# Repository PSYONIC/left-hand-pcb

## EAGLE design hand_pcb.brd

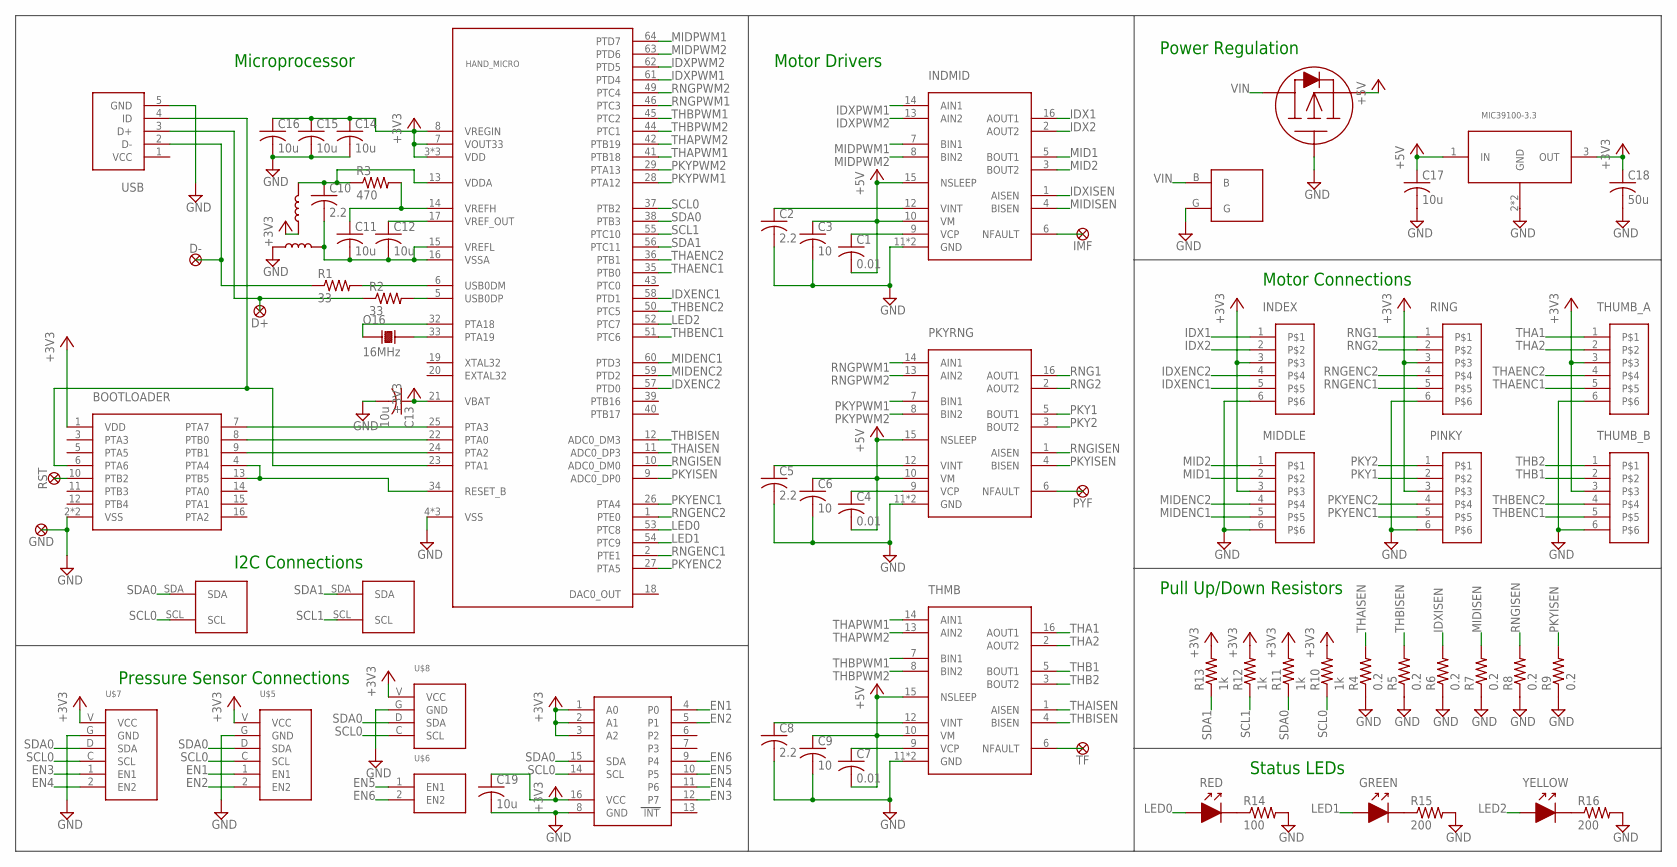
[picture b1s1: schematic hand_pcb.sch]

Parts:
BOOTLOADER: MKL02Z32CORRECT; QFN16
C1, C4, C7: 0.01; C0603
C2, C5, C8: 2.2; C0603
C3, C6, C9: 10; C0603
C10: 2.2; C0402
C11, C12, C13, C14, C15, C16, C19: 10u; C0402
C17: 10u; C0603
C18: 50u; C0603
D+: TESTPAD
D-: TESTPAD
GND: TESTPAD
GREEN: LED0603; L0603
HAND_MICRO: MK20DX256VLH7; LQFP-64-10-10
IMF: TESTPAD
INDEX: DF57H-6PTOP; DF57H-6P-TOP
INDMID: DRV8833; WQFN-16
MIDDLE: DF57H-6PTOP; DF57H-6P-TOP
O16: 16MHz; NX3225SA
PINKY: DF57H-6PTOP; DF57H-6P-TOP
PKYRNG: DRV8833; WQFN-16
PYF: TESTPAD
R1, R2: 33; R0402
R3: 470; R0402
R4, R5, R6, R7, R8, R9: 0.2; R1206
R10, R11, R12, R13: 1k; R0603
R14: 100; R0603
R15, R16: 200; R0603
RED: LED0603; L0603
RING: DF57H-6PTOP; DF57H-6P-TOP
RST: TESTPAD
TF: TESTPAD
THMB: DRV8833; WQFN-16
THUMB_A: DF57H-6PTOP; DF57H-6P-TOP
THUMB_B: DF57H-6PTOP; DF57H-6P-TOP
U$1: TCA9534TSSOP; TSSOP16
U$2: SPD15P10PLG; PG-TO-252-3
U$3, U$4: FERRITE600OHM100MHZ; L0603
U$5, U$7: PSENSE
U$6: PSENSE2
U$8: PSENSE4
U$9: MIC391003.3; MIC39100
U$10: THRUHOLE2
U$11, U$12: THRUHOLEI2C
USB: 10118194-0001LF
YELLOW: LED0603; L0603

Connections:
+3V3: BOOTLOADER.1 (VDD), C13.1, C14.1, C15.1, C16.1, C18.1, C19.1, HAND_MICRO.3 (VDD), HAND_MICRO.7 (VOUT33), HAND_MICRO.8 (VREGIN), HAND_MICRO.21 (VBAT), HAND_MICRO.30 (VDD), HAND_MICRO.48 (VDD), INDEX.3, MIDDLE.3, PINKY.3, R10.2, R11.2, R12.2, R13.2, RING.3, THUMB_A.3, THUMB_B.3, U$1.1 (A0), U$1.2 (A1), U$1.3 (A2), U$1.16 (VCC), U$4.1, U$5.V (VCC), U$7.V (VCC), U$8.V (VCC), U$9.3 (OUT)
+5V: C1.2, C3.1, C4.2, C6.1, C7.2, C9.1, C17.1, INDMID.10 (VM), INDMID.15 (NSLEEP), PKYRNG.10 (VM), PKYRNG.15 (NSLEEP), THMB.10 (VM), THMB.15 (NSLEEP), U$2.3, U$9.1 (IN)
EN1: U$1.4 (P0), U$5.1 (EN1)
EN2: U$1.5 (P1), U$5.2 (EN2)
EN3: U$1.12 (P7), U$7.1 (EN1)
EN4: U$1.11 (P6), U$7.2 (EN2)
EN5: U$1.10 (P5), U$6.1 (EN1)
EN6: U$1.9 (P4), U$6.2 (EN2)
GND: BOOTLOADER.2 (VSS), BOOTLOADER.TH (VSS), C2.2, C3.2, C5.2, C6.2, C8.2, C9.2, C13.2, C14.2, C15.2, C16.2, C17.2, C18.2, C19.2, GND.P$1, HAND_MICRO.4 (VSS), HAND_MICRO.31 (VSS), HAND_MICRO.47 (VSS), INDEX.6, INDMID.11 (GND), INDMID.PPAD (GND), MIDDLE.6, PINKY.6, PKYRNG.11 (GND), PKYRNG.PPAD (GND), R4.1, R5.1, R6.1, R7.1, R8.1, R9.1, R14.2, R15.2, R16.2, RING.6, THMB.11 (GND), THMB.PPAD (GND), THUMB_A.6, THUMB_B.6, U$1.8 (GND), U$2.1, U$3.1, U$5.G (GND), U$7.G (GND), U$8.G (GND), U$9.2 (GND), U$9.TAB (GND), U$10.G, USB.5 (GND)
IDX1: INDEX.1, INDMID.16 (AOUT1)
IDX2: INDEX.2, INDMID.2 (AOUT2)
IDXENC1: HAND_MICRO.58 (PTD1), INDEX.5
IDXENC2: HAND_MICRO.57 (PTD0), INDEX.4
IDXISEN: INDMID.1 (AISEN), R6.2
IDXPWM1: HAND_MICRO.61 (PTD4), INDMID.14 (AIN1)
IDXPWM2: HAND_MICRO.62 (PTD5), INDMID.13 (AIN2)
LED0: HAND_MICRO.53 (PTC8), RED.1
LED1: GREEN.1, HAND_MICRO.54 (PTC9)
LED2: HAND_MICRO.52 (PTC7), YELLOW.1
MID1: INDMID.5 (BOUT1), MIDDLE.2
MID2: INDMID.3 (BOUT2), MIDDLE.1
MIDENC1: HAND_MICRO.60 (PTD3), MIDDLE.5
MIDENC2: HAND_MICRO.59 (PTD2), MIDDLE.4
MIDISEN: INDMID.4 (BISEN), R7.2
MIDPWM1: HAND_MICRO.64 (PTD7), INDMID.7 (BIN1)
MIDPWM2: HAND_MICRO.63 (PTD6), INDMID.8 (BIN2)
unnamed: R14.1, RED.2
unnamed: GREEN.2, R15.1
unnamed: R16.1, YELLOW.2
unnamed: IMF.P$1, INDMID.6 (NFAULT)
unnamed: PKYRNG.6 (NFAULT), PYF.P$1
unnamed: TF.P$1, THMB.6 (NFAULT)
unnamed: C10.1, HAND_MICRO.13 (VDDA), R3.1, U$4.2
unnamed: BOOTLOADER.9 (PTB1), HAND_MICRO.24 (PTA2)
unnamed: C11.1, HAND_MICRO.14 (VREFH), R3.2
unnamed: BOOTLOADER.8 (PTB0), HAND_MICRO.22 (PTA0)
unnamed: BOOTLOADER.7 (PTA7), HAND_MICRO.25 (PTA3)
unnamed: BOOTLOADER.10 (PTB2), RST.P$1
unnamed: BOOTLOADER.4 (PTA4), BOOTLOADER.13 (PTB5), HAND_MICRO.34 (RESET_B)
unnamed: C10.2, C11.2, C12.2, HAND_MICRO.15 (VREFL), HAND_MICRO.16 (VSSA), U$3.2
unnamed: C1.1, INDMID.9 (VCP)
unnamed: C4.1, PKYRNG.9 (VCP)
unnamed: C7.1, THMB.9 (VCP)
unnamed: HAND_MICRO.33 (PTA19), O16.3
unnamed: C8.1, THMB.12 (VINT)
unnamed: C5.1, PKYRNG.12 (VINT)
unnamed: C2.1, INDMID.12 (VINT)
unnamed: HAND_MICRO.32 (PTA18), O16.1
unnamed: C12.1, HAND_MICRO.17 (VREF_OUT)
unnamed: BOOTLOADER.6 (PTA6), HAND_MICRO.23 (PTA1), USB.4 (ID)
PKY1: PINKY.2, PKYRNG.5 (BOUT1)
PKY2: PINKY.1, PKYRNG.3 (BOUT2)
PKYENC1: HAND_MICRO.26 (PTA4), PINKY.5
PKYENC2: HAND_MICRO.27 (PTA5), PINKY.4
PKYISEN: HAND_MICRO.9 (ADC0_DP0), PKYRNG.4 (BISEN), R9.2
PKYPWM1: HAND_MICRO.28 (PTA12), PKYRNG.7 (BIN1)
PKYPWM2: HAND_MICRO.29 (PTA13), PKYRNG.8 (BIN2)
RNG1: PKYRNG.16 (AOUT1), RING.1
RNG2: PKYRNG.2 (AOUT2), RING.2
RNGENC1: HAND_MICRO.2 (PTE1), RING.5
RNGENC2: HAND_MICRO.1 (PTE0), RING.4
RNGISEN: HAND_MICRO.10 (ADC0_DM0), PKYRNG.1 (AISEN), R8.2
RNGPWM1: HAND_MICRO.46 (PTC3), PKYRNG.14 (AIN1)
RNGPWM2: HAND_MICRO.49 (PTC4), PKYRNG.13 (AIN2)
SCL0: HAND_MICRO.37 (PTB2), R10.1, U$1.14 (SCL), U$5.C (SCL), U$7.C (SCL), U$8.C (SCL), U$11.SCL
SCL1: HAND_MICRO.55 (PTC10), R12.1, U$12.SCL
SDA0: HAND_MICRO.38 (PTB3), R11.1, U$1.15 (SDA), U$5.D (SDA), U$7.D (SDA), U$8.D (SDA), U$11.SDA
SDA1: HAND_MICRO.56 (PTC11), R13.1, U$12.SDA
THA1: THMB.16 (AOUT1), THUMB_A.1
THA2: THMB.2 (AOUT2), THUMB_A.2
THAENC1: HAND_MICRO.35 (PTB0), THUMB_A.5
THAENC2: HAND_MICRO.36 (PTB1), THUMB_A.4
THAISEN: HAND_MICRO.11 (ADC0_DP3), R4.2, THMB.1 (AISEN)
THAPWM1: HAND_MICRO.41 (PTB18), THMB.14 (AIN1)
THAPWM2: HAND_MICRO.42 (PTB19), THMB.13 (AIN2)
THB1: THMB.5 (BOUT1), THUMB_B.2
THB2: THMB.3 (BOUT2), THUMB_B.1
THBENC1: HAND_MICRO.51 (PTC6), THUMB_B.5
THBENC2: HAND_MICRO.50 (PTC5), THUMB_B.4
THBISEN: HAND_MICRO.12 (ADC0_DM3), R5.2, THMB.4 (BISEN)
THBPWM1: HAND_MICRO.45 (PTC2), THMB.7 (BIN1)
THBPWM2: HAND_MICRO.44 (PTC1), THMB.8 (BIN2)
USB_D1_N: D-.P$1, R1.1, USB.2 (D-)
USB_D1_P: D+.P$1, R2.1, USB.3 (D+)
USB_D2_N: HAND_MICRO.6 (USB0DM), R1.2
USB_D2_P: HAND_MICRO.5 (USB0DP), R2.2
VIN: U$2.2, U$10.B

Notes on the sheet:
Motor Drivers
Motor Connections
Power Regulation
Pull Up/Down Resistors
Pressure Sensor Connections
I2C Connections
Microprocessor
Status LEDs

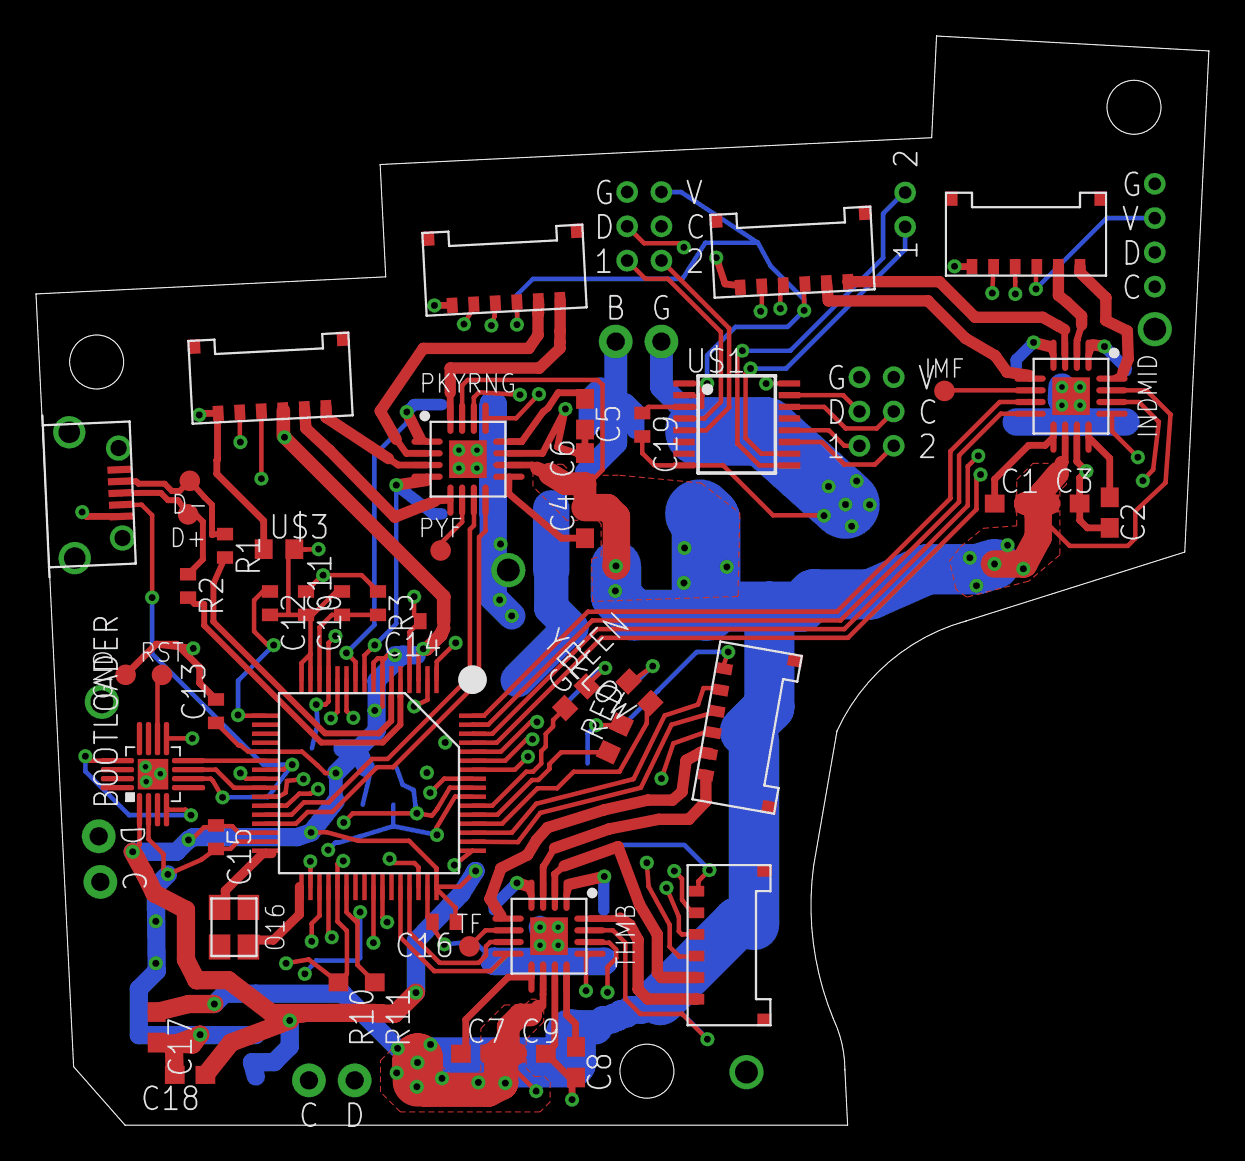
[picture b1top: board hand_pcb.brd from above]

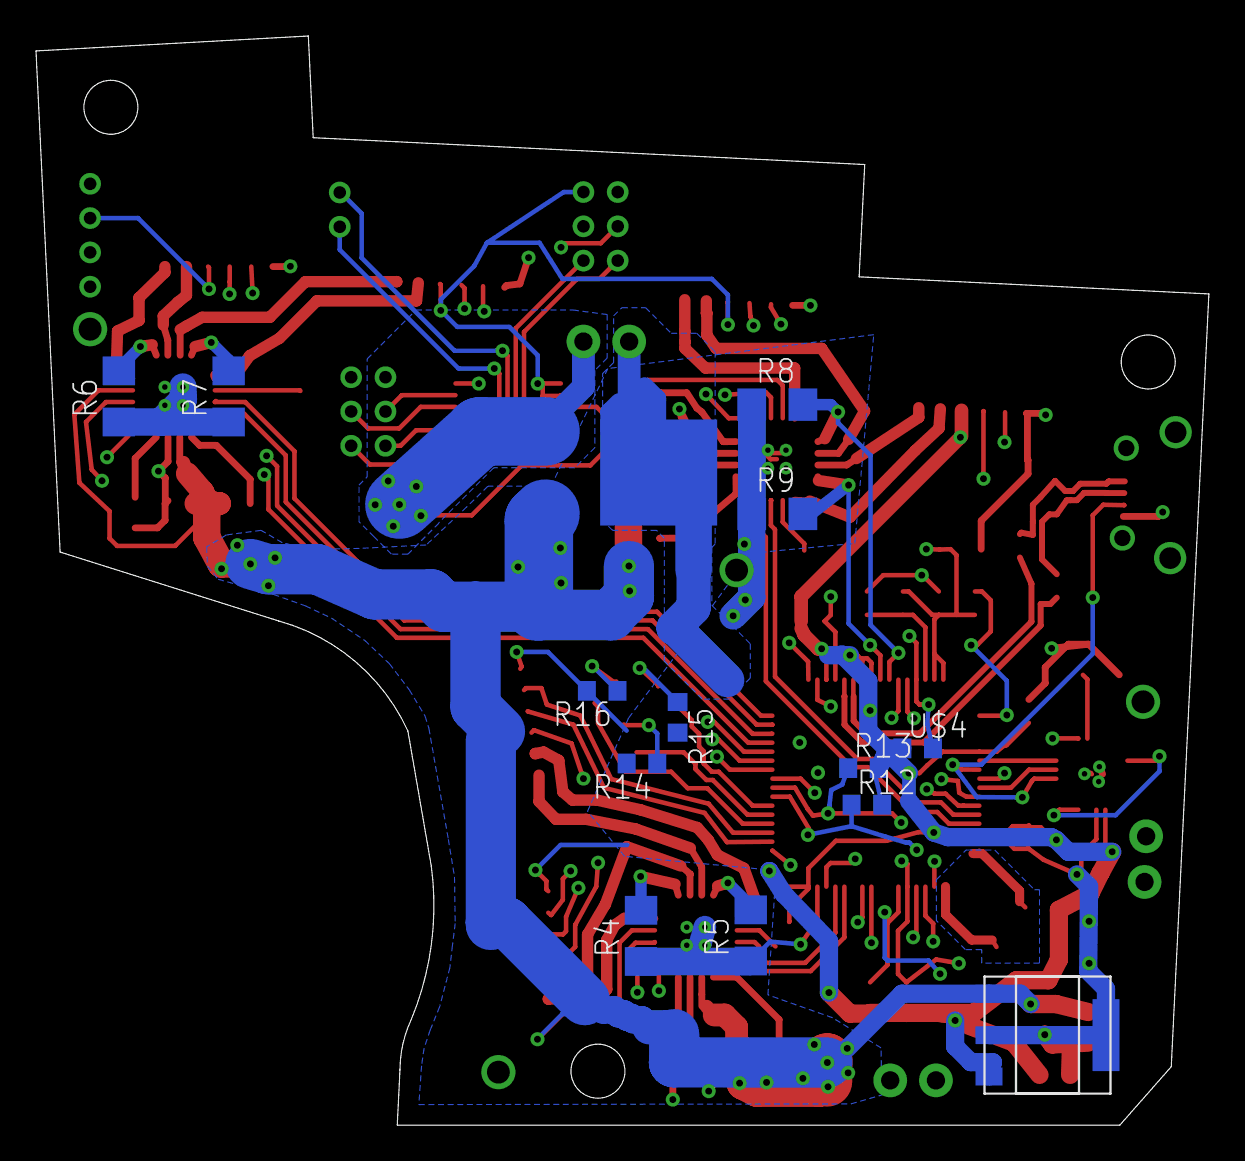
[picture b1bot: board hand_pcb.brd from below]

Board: 4 copper layers, 65.2 x 60.5 mm, 70 parts (14 on the bottom side), 87 nets.

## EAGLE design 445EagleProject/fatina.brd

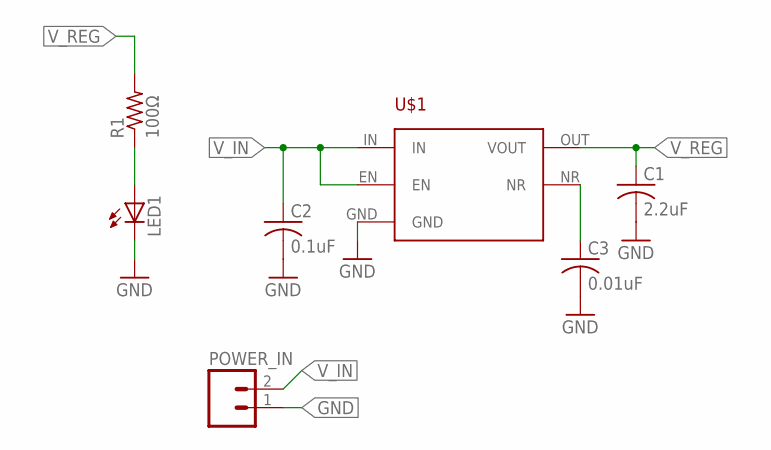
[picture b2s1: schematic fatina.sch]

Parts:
C1: 2.2uF; C0603
C2: 0.1uF; C0603
C3: 0.01uF; C0603
LED1: LED5MM
POWER_IN: M02PTH; 1X02
R1: 100Ω; 0204/7
U$1: TPS799

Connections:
GND: C1.2, C2.2, C3.2, LED1.K (C), POWER_IN.1, U$1.GND
unnamed: LED1.A, R1.1
unnamed: C3.1, U$1.NR
V_IN: C2.1, POWER_IN.2, U$1.EN, U$1.IN
V_REG: C1.1, R1.2, U$1.OUT (VOUT)

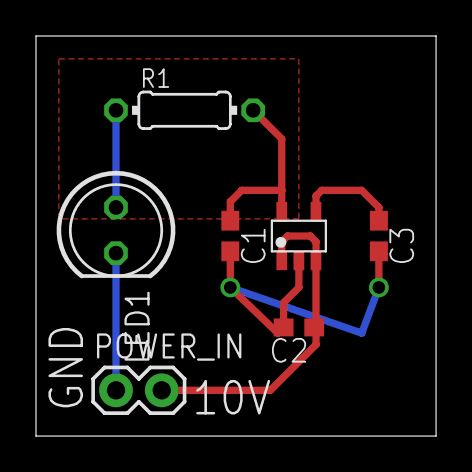
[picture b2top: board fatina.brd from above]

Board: 2 copper layers, 22.2 x 22.2 mm, 7 parts (0 on the bottom side), 5 nets.

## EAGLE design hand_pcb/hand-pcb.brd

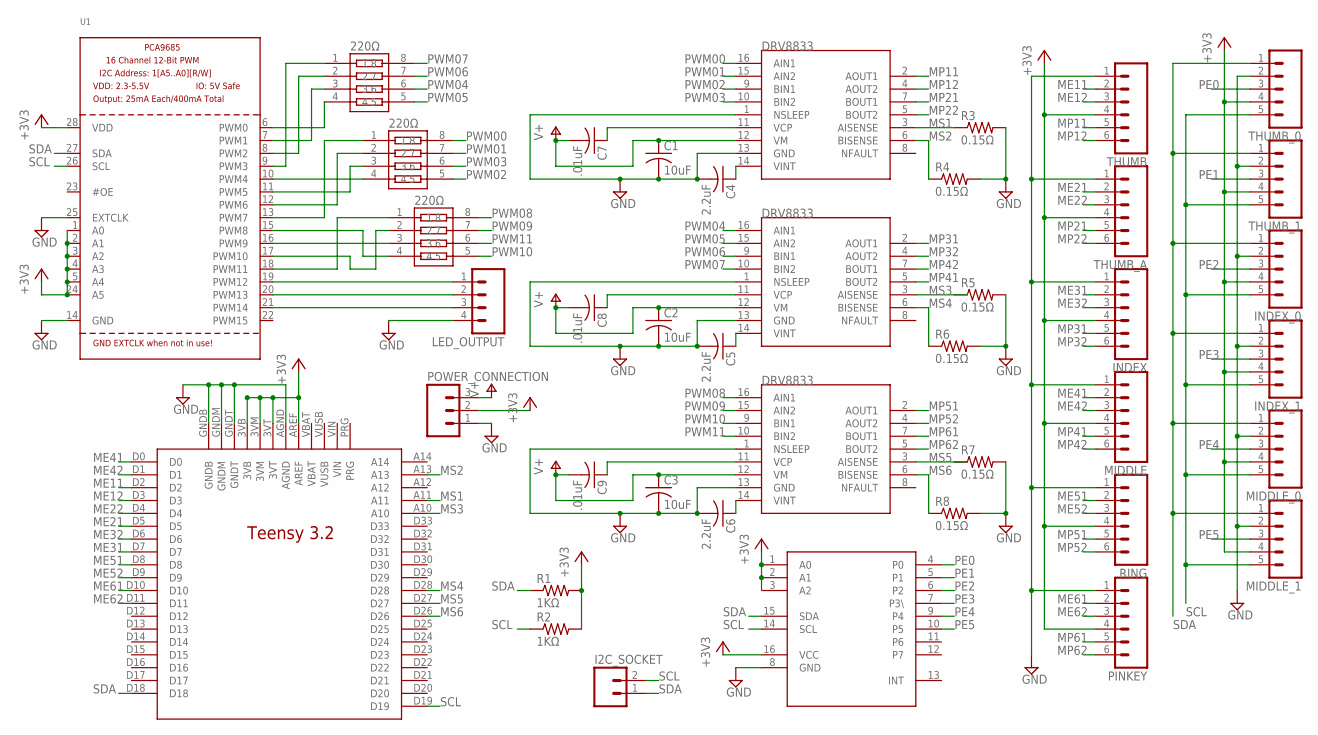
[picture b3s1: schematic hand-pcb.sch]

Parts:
220Ω: 220Ω; RP164PJ221CS
C1, C2, C3: 10uF; C0603
C4, C5, C6: 2.2uF; C0603
C7, C8, C9: .01uF; C0603
I2C_SOCKET: M02PTH; 1X02
INDEX: M06POGOPIN_HOLES_ONLY; 1X06_HOLES_ONLY
INDEX_0, INDEX_1: M05; 1X05_HOLES_ONLY
LED_OUTPUT: M04PTH; 1X04
MIDDLE: M06POGOPIN_HOLES_ONLY; 1X06_HOLES_ONLY
MIDDLE_0, MIDDLE_1: M05; 1X05_HOLES_ONLY
PINKEY: M06POGOPIN_HOLES_ONLY; 1X06_HOLES_ONLY
POWER_CONNECTION: M03PTH; 1X03
R1, R2: 1KΩ; R0603
R3, R4, R5, R6, R7, R8: 0.15Ω; M1206
RING: M06POGOPIN_HOLES_ONLY; 1X06_HOLES_ONLY
THUMB: M06POGOPIN_HOLES_ONLY; 1X06_HOLES_ONLY
THUMB_0, THUMB_1: M05; 1X05_HOLES_ONLY
THUMB_A: M06POGOPIN_HOLES_ONLY; 1X06_HOLES_ONLY
U1: PCA9685; TSSOP28
U$1, U$2, U$3: DRV8833; TSSOP16
U$4: TEENSY32
U$5: TCA9534TSS; TSSOP16
U$7, U$8: 220Ω; RP164PJ221CS

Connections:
+3V3: INDEX.4, INDEX_0.4, INDEX_1.4, MIDDLE.4, MIDDLE_0.4, MIDDLE_1.4, PINKEY.4, POWER_CONNECTION.2, R1.2, R2.2, RING.4, THUMB.4, THUMB_0.4, THUMB_1.4, THUMB_A.4, U1.1 (A0), U1.2 (A1), U1.3 (A2), U1.4 (A3), U1.5 (A4), U1.24 (A5), U1.28 (VDD), U$4.3VB, U$4.3VM, U$4.3VT, U$4.AREF, U$5.1 (A0), U$5.2 (A1), U$5.3 (A2), U$5.16 (VCC)
GND: C1.2, C2.2, C3.2, C4.2, C5.2, C6.2, INDEX.1, INDEX_0.2, INDEX_1.2, LED_OUTPUT.4, MIDDLE.1, MIDDLE_0.2, MIDDLE_1.2, PINKEY.1, POWER_CONNECTION.1, R3.2, R4.2, R5.2, R6.2, R7.2, R8.2, RING.1, THUMB.1, THUMB_0.2, THUMB_1.2, THUMB_A.1, U1.14 (GND), U1.25 (EXTCLK), U$1.1 (NSLEEP), U$1.13 (GND), U$2.1 (NSLEEP), U$2.13 (GND), U$3.1 (NSLEEP), U$3.13 (GND), U$4.AGND, U$4.GNDB, U$4.GNDM, U$4.GNDT, U$5.8 (GND)
ME11: THUMB.2, U$4.D2
ME12: THUMB.3, U$4.D3
ME21: THUMB_A.2, U$4.D5
ME22: THUMB_A.3, U$4.D4
ME31: INDEX.2, U$4.D7
ME32: INDEX.3, U$4.D6
ME41: MIDDLE.2, U$4.D0
ME42: MIDDLE.3, U$4.D1
ME51: RING.2, U$4.D8
ME52: RING.3, U$4.D9
ME61: PINKEY.2, U$4.D10
ME62: PINKEY.3, U$4.D11
MP11: THUMB.5, U$1.2 (AOUT1)
MP12: THUMB.6, U$1.4 (AOUT2)
MP21: THUMB_A.5, U$1.7 (BOUT1)
MP22: THUMB_A.6, U$1.5 (BOUT2)
MP31: INDEX.5, U$2.2 (AOUT1)
MP32: INDEX.6, U$2.4 (AOUT2)
MP41: MIDDLE.5, U$2.5 (BOUT2)
MP42: MIDDLE.6, U$2.7 (BOUT1)
MP51: RING.5, U$3.2 (AOUT1)
MP52: RING.6, U$3.4 (AOUT2)
MP61: PINKEY.5, U$3.7 (BOUT1)
MP62: PINKEY.6, U$3.5 (BOUT2)
MS1: R3.1, U$1.3 (AISENSE), U$4.A11
MS2: R4.1, U$1.6 (BISENSE), U$4.A13
MS3: R5.1, U$2.3 (AISENSE), U$4.A10
MS4: R6.1, U$2.6 (BISENSE), U$4.D28
MS5: R7.1, U$3.3 (AISENSE), U$4.D27
MS6: R8.1, U$3.6 (BISENSE), U$4.D26
unnamed: 220Ω.4, U1.6 (PWM0)
unnamed: 220Ω.3, U1.7 (PWM1)
unnamed: 220Ω.2, U1.8 (PWM2)
unnamed: 220Ω.1, U1.9 (PWM3)
unnamed: U1.10 (PWM4), U$7.4
unnamed: U1.11 (PWM5), U$7.3
unnamed: U1.12 (PWM6), U$7.2
unnamed: U1.13 (PWM7), U$7.1
unnamed: U1.15 (PWM8), U$8.4
unnamed: U1.16 (PWM9), U$8.3
unnamed: U1.17 (PWM10), U$8.2
unnamed: U1.18 (PWM11), U$8.1
unnamed: C7.1, U$1.11 (VCP)
unnamed: C8.1, U$2.11 (VCP)
unnamed: C9.1, U$3.11 (VCP)
unnamed: LED_OUTPUT.1, U1.19 (PWM12)
unnamed: LED_OUTPUT.2, U1.20 (PWM13)
unnamed: LED_OUTPUT.3, U1.21 (PWM14)
unnamed: C4.1, U$1.14 (VINT)
unnamed: C5.1, U$2.14 (VINT)
unnamed: C6.1, U$3.14 (VINT)
PE0: THUMB_0.3, U$5.4 (P0)
PE1: THUMB_1.3, U$5.5 (P1)
PE2: INDEX_0.3, U$5.6 (P2)
PE3: INDEX_1.3, U$5.7 (P3\)
PE4: MIDDLE_0.3, U$5.9 (P4)
PE5: MIDDLE_1.3, U$5.10 (P5)
PRG: U$4.PRG
PWM00: U$1.16 (AIN1), U$7.8
PWM01: U$1.15 (AIN2), U$7.7
PWM02: U$1.9 (BIN1), U$7.5
PWM03: U$1.10 (BIN2), U$7.6
PWM04: 220Ω.6, U$2.16 (AIN1)
PWM05: 220Ω.5, U$2.15 (AIN2)
PWM06: 220Ω.7, U$2.9 (BIN1)
PWM07: 220Ω.8, U$2.10 (BIN2)
PWM08: U$3.16 (AIN1), U$8.8
PWM09: U$3.15 (AIN2), U$8.7
PWM10: U$3.9 (BIN1), U$8.5
PWM11: U$3.10 (BIN2), U$8.6
SCL: I2C_SOCKET.2, INDEX_0.5, INDEX_1.5, MIDDLE_0.5, MIDDLE_1.5, R2.1, THUMB_0.5, THUMB_1.5, U1.26 (SCL), U$4.D19, U$5.14 (SCL)
SDA: I2C_SOCKET.1, INDEX_0.1, INDEX_1.1, MIDDLE_0.1, MIDDLE_1.1, R1.1, THUMB_0.1, THUMB_1.1, U1.27 (SDA), U$4.D18, U$5.15 (SDA)
V+: C1.1, C2.1, C3.1, C7.2, C8.2, C9.2, POWER_CONNECTION.3, U$1.12 (VM), U$2.12 (VM), U$3.12 (VM)
VBAT: U$4.VBAT
VIN: U$4.VIN
VUSB: U$4.VUSB

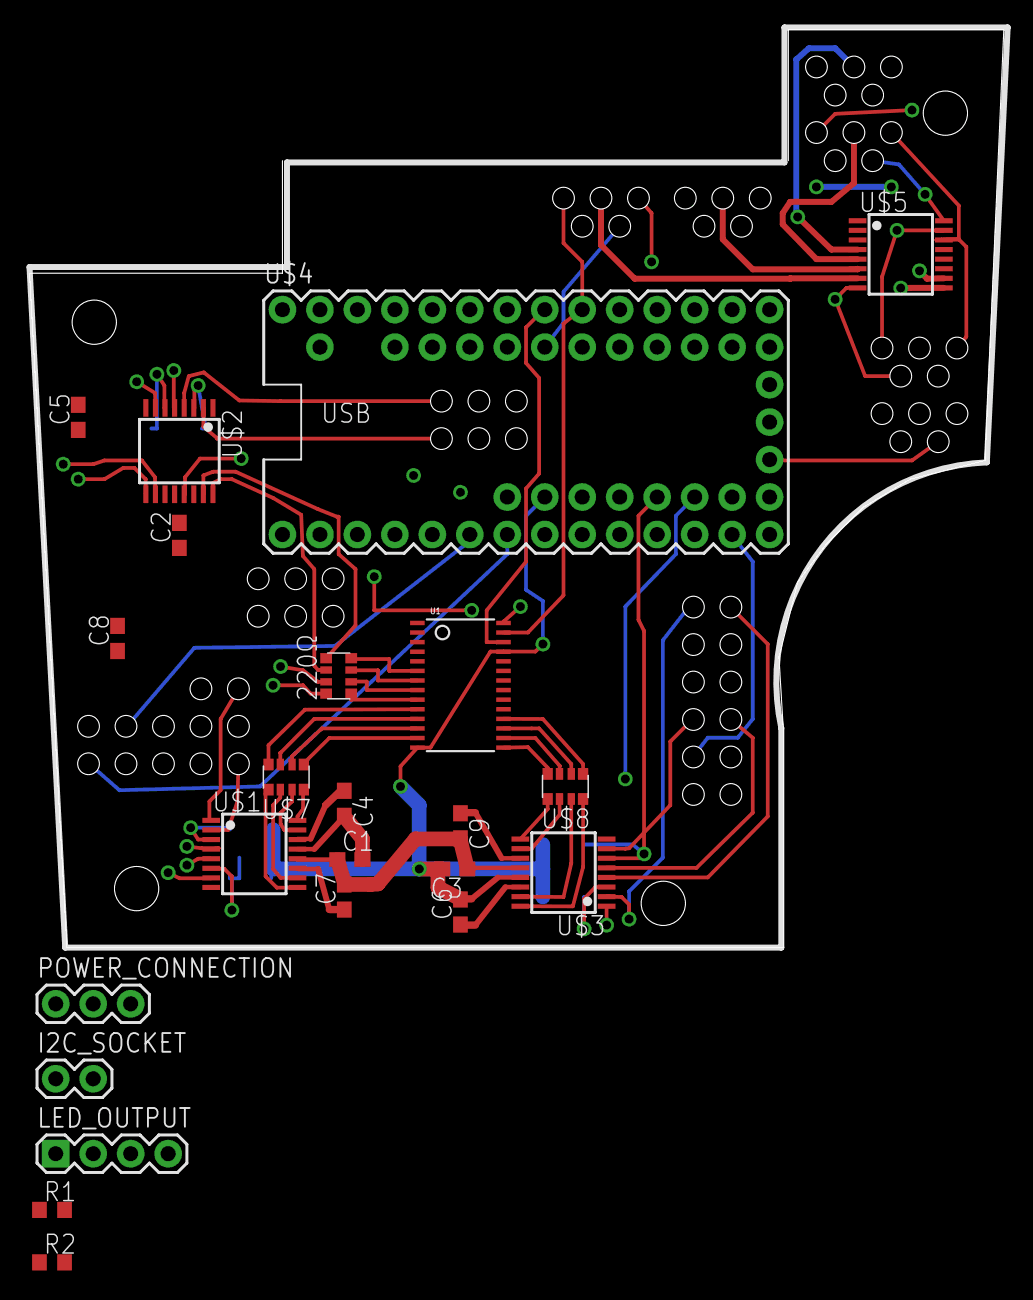
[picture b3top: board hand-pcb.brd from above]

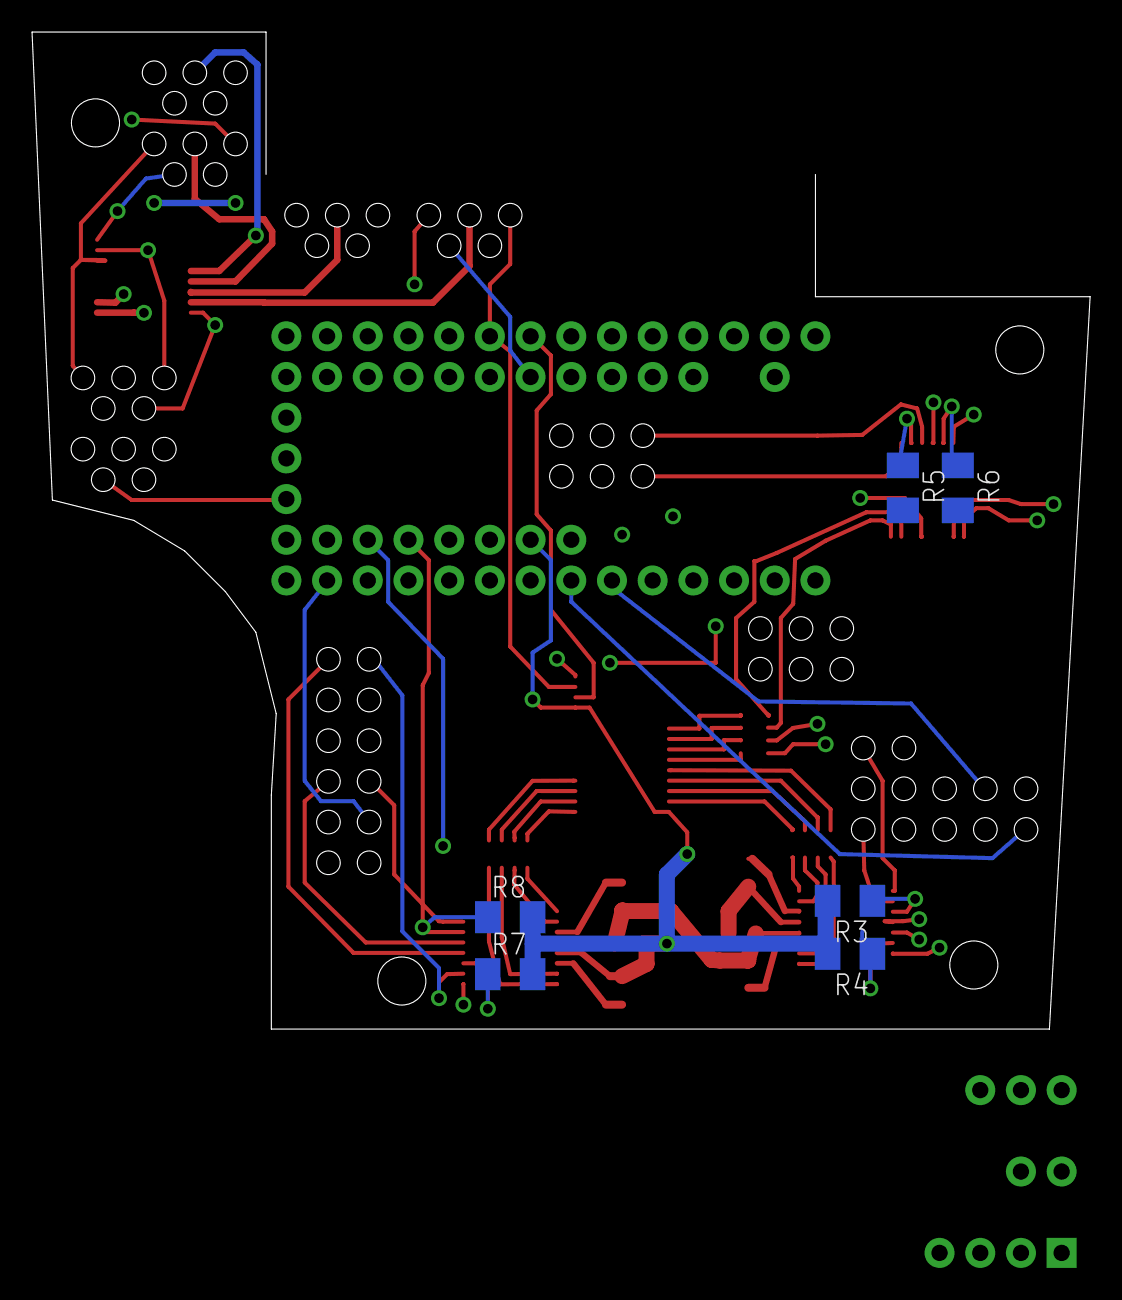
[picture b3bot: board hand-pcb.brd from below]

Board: 4 copper layers, 66.0 x 62.2 mm, 41 parts (6 on the bottom side), 74 nets.

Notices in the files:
parts and their libraries:
SparkFun1: Licensing: CC v3.0 Share-Alike You are welcome to use this library for commercial purposes.
